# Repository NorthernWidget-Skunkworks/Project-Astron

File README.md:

# Project-Astron
Eagle files for a breakout module to test the capability of low cost RTC systems

<br>
<br />This work is licensed under a <a rel="license" href="http://creativecommons.org/licenses/by-sa/4.0/">Creative Commons Attribution-ShareAlike 4.0 International License</a>.

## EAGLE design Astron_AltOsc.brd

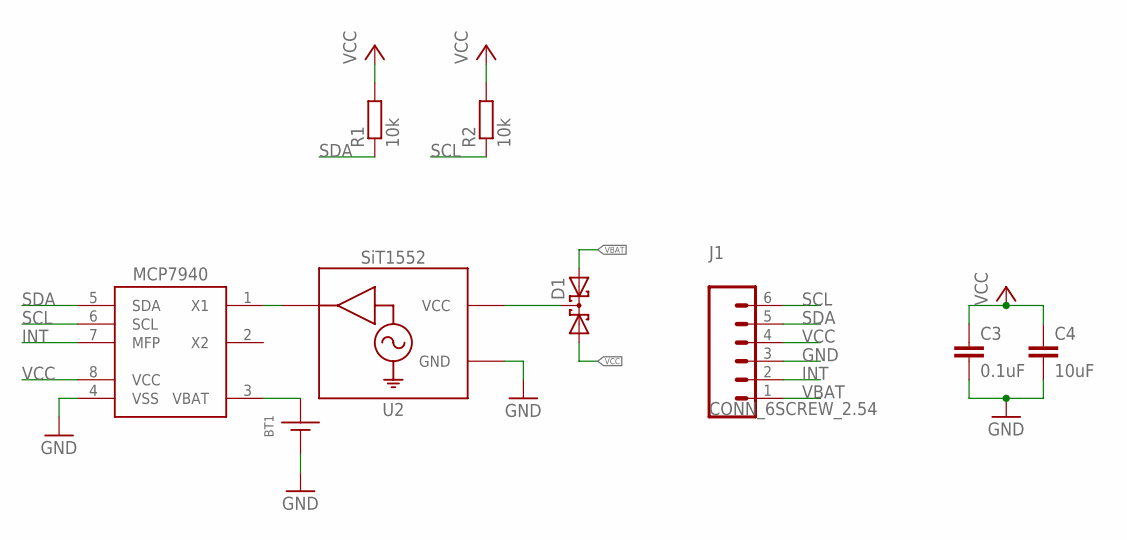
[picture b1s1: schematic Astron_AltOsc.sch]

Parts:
BT1: BATTERY_COIN12MM; LINX_BAT-HLD-012-SMT
C3: 0.1uF; C0603
C4: 10uF; C0805
D1: DIODE_CCBAT54CSOT23; SOT23-3
J1: CONN_6SCREW_2.54; 1X06_SCREW
R1, R2: 10k; R0603
U1: MCP7940SOIC; SO08
U2: SIT1552; LD-4

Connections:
GND: BT1.GND (-), C3.2, C4.2, J1.3, U1.4 (VSS), U2.1 (GND), U2.4 (GND)
INT: J1.2, U1.7 (MFP)
unnamed: U1.1 (X1), U2.2 (CLK)
unnamed: D1.3 (C), U2.3 (VCC)
SCL: J1.6, R2.1, U1.6 (SCL)
SDA: J1.5, R1.1, U1.5 (SDA)
VBAT: BT1.POWER0 (+), BT1.POWER1 (+), D1.2 (A2), J1.1, U1.3 (VBAT)
VCC: C3.1, C4.1, D1.1 (A1), J1.4, R1.2, R2.2, U1.8 (VCC)

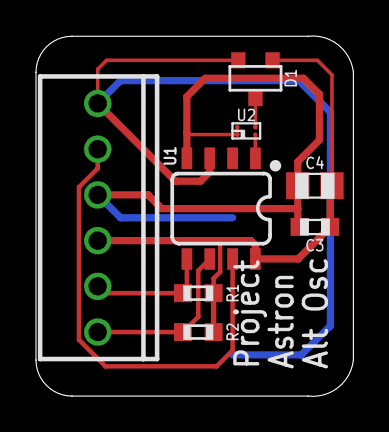
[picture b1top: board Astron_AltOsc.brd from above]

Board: 2 copper layers, 17.6 x 20.0 mm, 9 parts (1 on the bottom side), 8 nets.

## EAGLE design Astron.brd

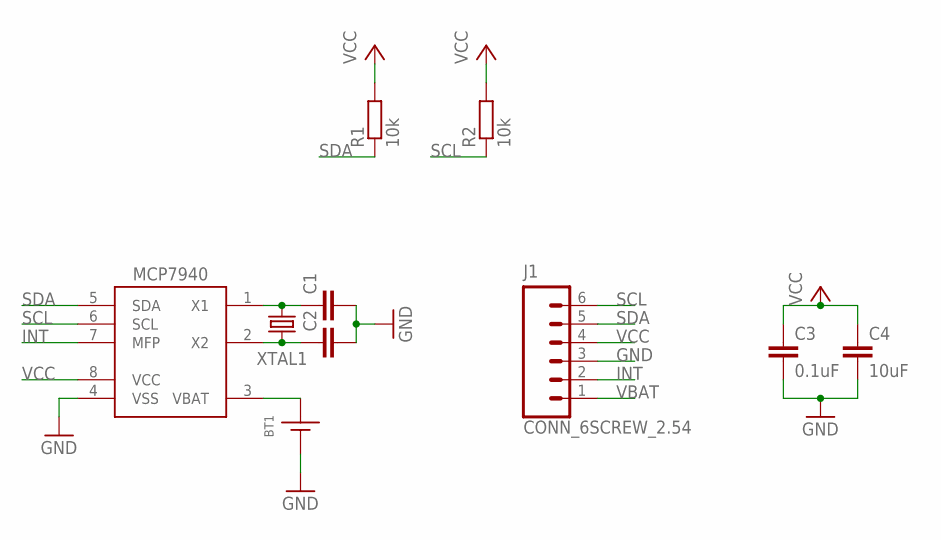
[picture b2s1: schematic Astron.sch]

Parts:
BT1: BATTERY_COIN12MM; LINX_BAT-HLD-012-SMT
C1, C2: C-EUC0603; C0603
C3: 0.1uF; C0603
C4: 10uF; C0805
J1: CONN_6SCREW_2.54; 1X06_SCREW
R1, R2: 10k; R0603
U$1: MCP7940SOIC; SO08
XTAL1: CRYSTAL3.2X1.5; CRYSTAL_3.2X1.5_2-SMD

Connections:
GND: BT1.GND (-), C1.2, C2.2, C3.2, C4.2, J1.3, U$1.4 (VSS)
INT: J1.2, U$1.7 (MFP)
unnamed: C1.1, U$1.1 (X1), XTAL1.P$1 (1)
unnamed: C2.1, U$1.2 (X2), XTAL1.P$2 (2)
SCL: J1.6, R2.1, U$1.6 (SCL)
SDA: J1.5, R1.1, U$1.5 (SDA)
VBAT: BT1.POWER0 (+), BT1.POWER1 (+), J1.1, U$1.3 (VBAT)
VCC: C3.1, C4.1, J1.4, R1.2, R2.2, U$1.8 (VCC)

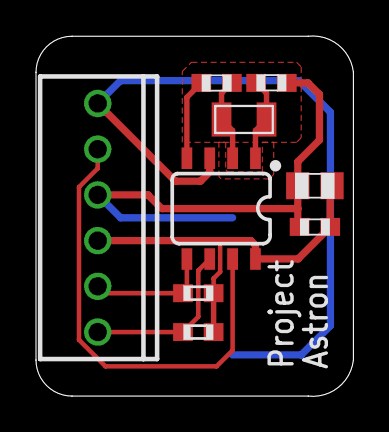
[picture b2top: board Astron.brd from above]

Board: 2 copper layers, 17.6 x 20.0 mm, 10 parts (1 on the bottom side), 8 nets.

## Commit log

2018-04-12 Initial comit, preliminary board layout done
2018-04-16 Generated gerbers, minor edits
2018-12-18 CC-BY-SA
2024-11-02 Minor updates and added gerber
